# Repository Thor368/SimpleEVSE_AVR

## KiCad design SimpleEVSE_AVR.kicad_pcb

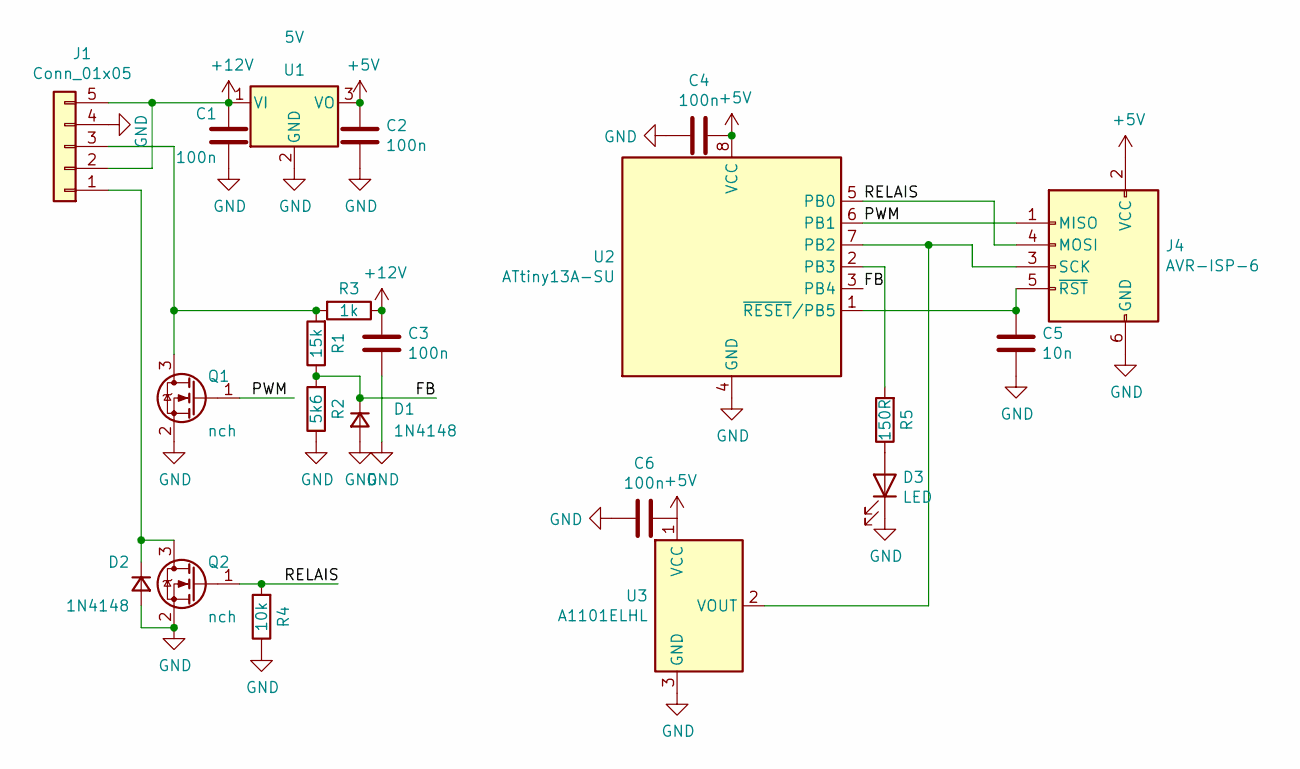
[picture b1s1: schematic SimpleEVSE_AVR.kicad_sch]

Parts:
C1, C2, C3, C4, C6: 100n; C_0805_2012Metric
C5: 10n; C_0805_2012Metric
D1, D2: 1N4148; D_SOD-123
D3: LED; LED_0805_2012Metric
J1: Conn_01x05; PinHeader_1x05_P2.54mm_Horizontal
J4: AVR-ISP-6; PinHeader_2x03_P2.54mm_Vertical
Q1, Q2: nch; SOT-23
R1: 15k; R_0805_2012Metric
R2: 5k6; R_0805_2012Metric
R3: 1k; R_0805_2012Metric
R4: 10k; R_0805_2012Metric
R5: 150R; R_0805_2012Metric
U1: 5V; SOT-223-3_TabPin2
U2: ATtiny13A-SU; SOIJ-8_5.3x5.3mm_P1.27mm
U3: A1101ELHL; SOT-23

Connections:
+5V: C2.2, C4.2, C6.1, J4.2 (VCC), U1.3 (VO), U2.8 (VCC), U3.1 (VCC)
+12V: C1.2, C3.1, J1.2, J1.5, R3.1, U1.1 (VI)
/FB: D1.1 (K), R1.1, R2.2, U2.3 (PB4)
/PWM: J4.1 (MISO), Q1.1 (G), U2.6 (PB1)
/RELAIS: J4.4 (MOSI), Q2.1 (G), R4.2, U2.5 (PB0)
GND: C1.1, C2.1, C3.2, C4.1, C5.2, C6.2, D1.2 (A), D2.2 (A), D3.1 (K), J1.4, J4.6 (GND), Q1.2 (S), Q2.2 (S), R2.1, R4.1, U1.2 (GND), U2.4 (GND), U3.3 (GND)
unnamed: D2.1 (K), J1.1, Q2.3 (D)
unnamed: D3.2 (A), R5.1
unnamed: J1.3, Q1.3 (D), R1.2, R3.2
unnamed: J4.3 (SCK), U2.7 (PB2), U3.2 (VOUT)
unnamed: C5.1, J4.5 (~RST), U2.1 (~RESET/PB5)
unnamed: R5.2, U2.2 (PB3)

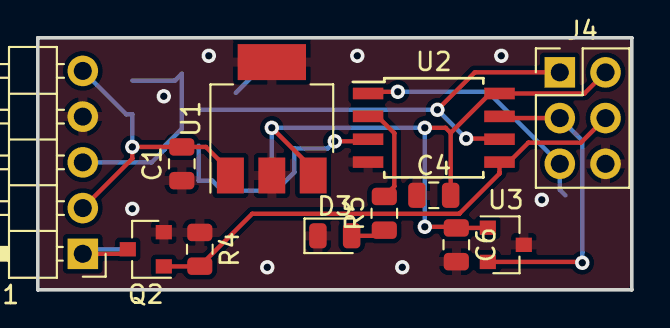
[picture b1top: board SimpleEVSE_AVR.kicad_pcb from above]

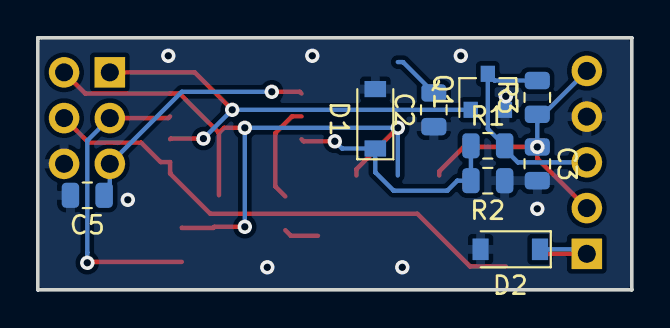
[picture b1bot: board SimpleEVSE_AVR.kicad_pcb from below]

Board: 2 copper layers, 33.0 x 14.0 mm, 21 parts (9 on the bottom side), 12 nets.

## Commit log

2019-06-11 - simple EVSE with an AVR ATtiny13
2019-06-28 - set zeros - added ignore file
2023-04-12 - updated to KiCAD v6.0
2025-05-01 - update to KiCAD 8
2025-06-22 - updated to KiCAD9 - changed LDO from MEA to EMA
